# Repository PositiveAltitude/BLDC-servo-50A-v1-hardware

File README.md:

# 50A BLDC Servo Motor
This is an attempt to create a servomotor board for BLDC motors capable of providing 50A continuous current. 

Work in progress...

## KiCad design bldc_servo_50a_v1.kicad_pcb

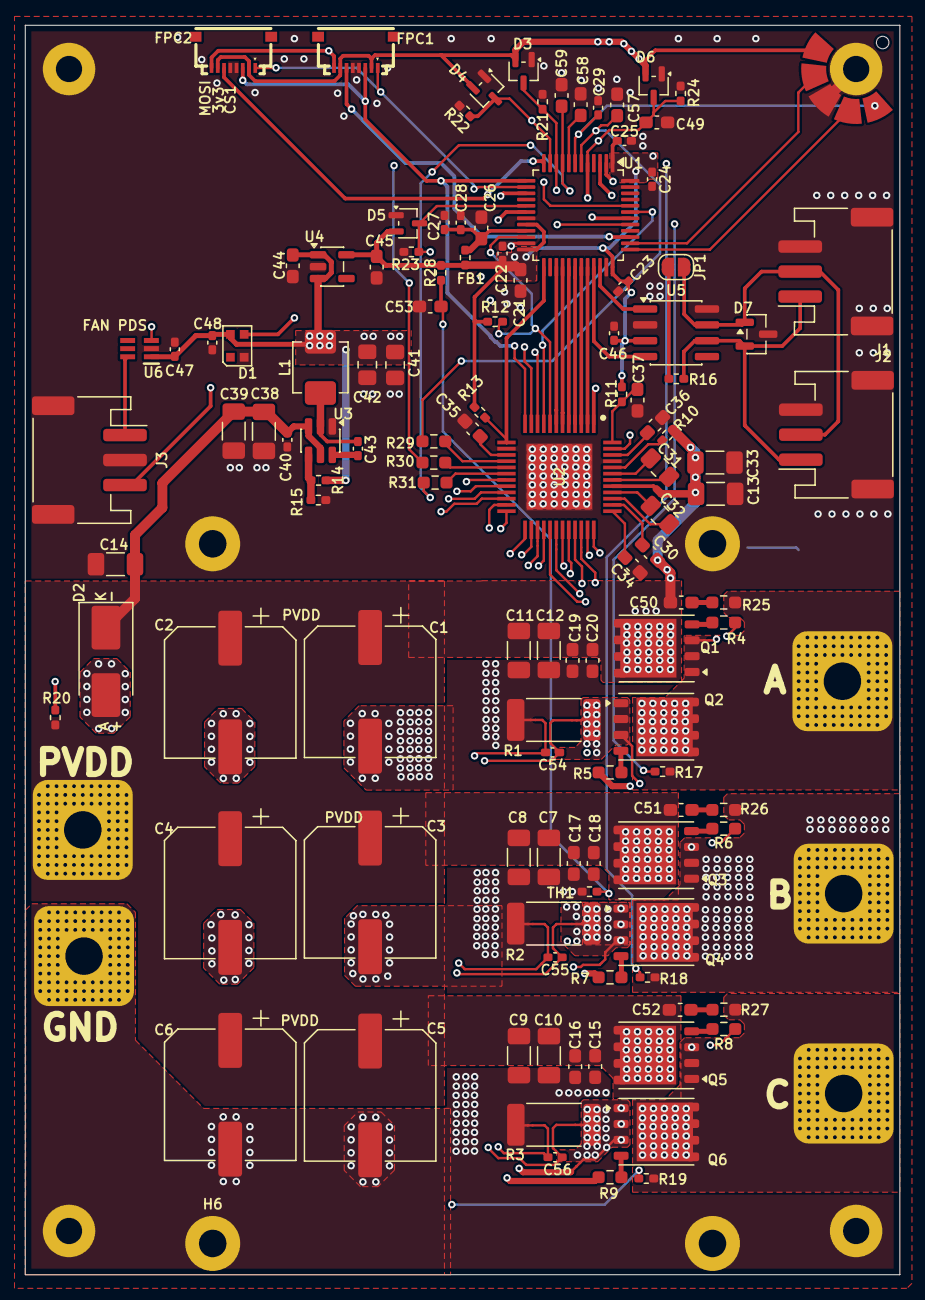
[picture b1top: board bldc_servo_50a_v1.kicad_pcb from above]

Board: 4 copper layers, 70.0 x 100.0 mm, 143 parts (0 on the bottom side), 90 nets.

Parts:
C1, C2, C3, C4, C5, C6: 100u; CP_Elec_10x7.9
C7, C8, C9, C10, C11, C12, C13, C14, C33, C38, C39: 4.7u; C_1206_3216Metric_Pad1.33x1.80mm_HandSolder
C15, C16, C17, C18, C19, C20, C26, C34, C35, C36, C37, C44, C45, C49, C53, C57, C58, C59: 1u; C_0603_1608Metric_Pad1.08x0.95mm_HandSolder
C21: 4.7u; C_0603_1608Metric_Pad1.08x0.95mm_HandSolder
C22, C23, C24, C25, C27, C29, C40, C43, C46, C47, C48: 100n; C_0402_1005Metric_Pad0.74x0.62mm_HandSolder
C28: 10n; C_0402_1005Metric_Pad0.74x0.62mm_HandSolder
C30: 2.2u; C_0603_1608Metric_Pad1.08x0.95mm_HandSolder
C31, C32: 47n; C_0805_2012Metric_Pad1.18x1.45mm_HandSolder
C41, C42: 22u; C_0805_2012Metric_Pad1.18x1.45mm_HandSolder
C50, C51, C52: 1n; C_0603_1608Metric_Pad1.08x0.95mm_HandSolder
C54, C55, C56: 1n; C_0402_1005Metric_Pad0.74x0.62mm_HandSolder
D1: WS2812B-2020; LED_WS2812B-2020_PLCC4_2.0x2.0mm
D2: SMBJ28A; D_SMB_Handsoldering
D3, D4, D5, D6: BAT54SW; SOT-323_SC-70
D7: SM712_SOT23; SOT-23
FB1: BLM15AG601SN1D; R_0402_1005Metric_Pad0.72x0.64mm_HandSolder
FPC1: Encoder1; FPC-SMD_8P-P0.50_HC-FPC-05-09-8RLTAG
FPC2: Encoder2; FPC-SMD_8P-P0.50_HC-FPC-05-09-8RLTAG
H1, H2, H3: Positive_Altitude_M2_Hole
H4, H5, H6, H7: MountingHole_2.2mm_M2_Pad
J1: CAN1; JST_PH_S3B-PH-SM4-TB_1x03-1MP_P2.00mm_Horizontal
J2: CAN2; JST_PH_S3B-PH-SM4-TB_1x03-1MP_P2.00mm_Horizontal
J3: FAN; JST_PH_S3B-PH-SM4-TB_1x03-1MP_P2.00mm_Horizontal
J5: SWD; Positive_Altitude_SWD_Connector
JP1: Enable_CAN_Termination_1; SolderJumper-2_P1.3mm_Open_RoundedPad1.0x1.5mm
L1: 3.3u; L_Changjiang_FXL0420
NT1, NT2, NT3, NT4, NT5, NT6, NT7, NT8, NT9, NT10, NT11, NT12: NetTie_2; NetTie-2_SMD_Pad0.2mm
P1: PVDD; Soldering_Pad_8mm_3mm_hole
P2: GND; Soldering_Pad_8mm_3mm_hole
P3: PHASE_A; Soldering_Pad_8mm_3mm_hole
P4: PHASE_B; Soldering_Pad_8mm_3mm_hole
P5: PHASE_C; Soldering_Pad_8mm_3mm_hole
Q1, Q2, Q3, Q4, Q5, Q6: BSC010N04LS; Infineon_PG-TDSON-8_6.15x5.15mm
R1, R2, R3: 1m; R_2512_6332Metric_Pad1.40x3.35mm_HandSolder
R4, R5, R6, R7, R8, R9: 2.2; R_0603_1608Metric_Pad0.98x0.95mm_HandSolder
R10: 100; R_0402_1005Metric_Pad0.72x0.64mm_HandSolder
R11: 220; R_0402_1005Metric_Pad0.72x0.64mm_HandSolder
R12, R13, R28: 10k; R_0402_1005Metric_Pad0.72x0.64mm_HandSolder
R14: 100k; R_0402_1005Metric_Pad0.72x0.64mm_HandSolder
R15: 13.7k; R_0402_1005Metric_Pad0.72x0.64mm_HandSolder
R16: 120; R_0402_1005Metric_Pad0.72x0.64mm_HandSolder
R17, R18, R19, R20: 39k; R_0402_1005Metric_Pad0.72x0.64mm_HandSolder
R21, R22, R23, R24: 5k; R_0402_1005Metric_Pad0.72x0.64mm_HandSolder
R25, R26, R27: 10; R_0603_1608Metric_Pad0.98x0.95mm_HandSolder
R29, R30, R31: 100; R_0603_1608Metric_Pad0.98x0.95mm_HandSolder
TH1: NCP15XH103F03RC; R_0402_1005Metric_Pad0.72x0.64mm_HandSolder
U1: STM32G431CBT6; LQFP-48_7x7mm_P0.5mm
U2: DRV8305NQPHPRQ1; QFP50P900X900X120-49N
U3: LMR51430; SOT-23-6
U4: TLV75533PDBV; SOT-23-5
U5: SN65HVD230; SOIC-8_3.9x4.9mm_P1.27mm
U6: TPS22919DCKR; SOT65P210X110-6N

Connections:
+3.3V: C21.2, C22.2, C23.2, C24.2, C25.2, C45.1, C46.1, D3.2 (K), D4.2 (K), D5.2 (K), D6.2 (K), FB1.1, FPC1.2, FPC1.7, FPC2.2, FPC2.7, J5.1 (+3.3V), R11.1, R12.1, R13.1, R28.1, U1.1 (VBAT), U1.20 (VREF+), U1.24 (VDD), U1.36 (VDD), U1.48 (VDD), U4.5 (OUT), U5.3 (VCC)
+3.3VA: C26.1, C27.1, C28.1, FB1.2, U1.21 (VDDA)
+5V: C41.1, C42.1, C44.1, C47.1, C48.2, D1.4 (VDD), L1.1, R14.1, U4.1 (IN), U4.3 (EN), U6.1 (IN)
/5V_BOOT: C43.2, U3.6 (CB)
/5V_FB: R14.2, R15.1, U3.4 (FB)
/5V_SW: C43.1, L1.2, U3.2 (SW)
/CAN_H: D7.1 (A1), J1.2, J2.2, JP1.2 (B), U5.7 (CANH)
/CAN_L: D7.2 (A2), J1.1, J2.1, R16.2, U5.6 (CANL)
/CAN_RX: U1.33 (PA11), U5.4 (R)
/CAN_TX: U1.34 (PA12), U5.1 (D)
/CS_1: FPC2.6, U1.12 (PA4)
/CS_2: FPC1.6, U1.39 (PA15)
/DRV_AVDD: C35.1, U2.15 (AVDD)
/DRV_CP1H: C31.1, U2.43 (CP1H)
/DRV_CP1L: C31.2, U2.42 (CP1L)
/DRV_CP2H: C32.1, U2.39 (CP2H)
/DRV_CP2L: C32.2, U2.40 (CP2L)
/DRV_CS: U1.43 (PB6), U2.9 (NSCS)
/DRV_DVDD: C36.1, U2.46 (DVDD)
/DRV_NFAULT: R12.2, U1.22 (PB10), U2.8 (NFAULT)
/DRV_PWRGD: R13.2, U1.25 (PB11), U2.13 (PWRGD)
/DRV_VCPH: C30.1, U2.38 (VCPH)
/DRV_VCP_LSD: C34.1, U2.37 (VCP_LSD)
/DRV_VDRAIN: R10.2, U2.44 (VDRAIN)
/DRV_VREG: C37.1, R11.2, U2.48 (VREG)
/DRV_WAKE: U1.3 (PC14), U2.47 (WAKE)
/EN_GATE: U1.2 (PC13), U2.1 (EN_GATE)
/FAN_5V: J3.1, U6.6 (OUT)
/FAN_EN: U1.44 (PB7), U6.3 (ON)
/FAN_PWM: J3.3, U1.41 (PB4)
/GH_A: R4.1, U2.36 (GHA)
/GH_B: R6.1, U2.29 (GHB)
/GH_C: R8.1, U2.28 (GHC)
/GL_A: R5.1, U2.33 (GLA)
/GL_B: R7.1, U2.32 (GLB)
/GL_C: R9.1, U2.25 (GLC)
/INHA: U1.32 (PA10), U2.2 (INHA)
/INHB: U1.30 (PA8), U2.4 (INHB)
/INHC: U1.28 (PB14), U2.6 (INHC)
/INLA: U1.31 (PA9), U2.3 (INLA)
/INLB: U1.29 (PB15), U2.5 (INLB)
/INLC: U1.27 (PB13), U2.7 (INLC)
/LED: D1.3 (DIN), U1.42 (PB5)
/MISO: FPC1.1, FPC2.1, U1.14 (PA6), U2.11 (SDO)
/MOSI: FPC1.8, FPC2.8, U1.15 (PA7), U2.10 (SDI)
/NRST: C29.1, J5.5 (RESET), U1.7 (PG10)
/PHASE_A: NT3.2, P3.1 (1_1), Q1.1 (S_1), Q1.2 (S_2), Q1.3 (S_3), Q2.5 (D_1), R17.1, R25.1
/PHASE_A_SENSE: D3.3 (COM), R17.2, R21.1, U1.10 (PA2)
/PHASE_B: NT8.2, P4.1 (1_1), Q3.1 (S_1), Q3.2 (S_2), Q3.3 (S_3), Q4.5 (D_1), R18.1, R26.1
/PHASE_B_SENSE: D4.3 (COM), R18.2, R22.1, U1.11 (PA3)
/PHASE_C: NT12.2, P5.1 (1_1), Q5.1 (S_1), Q5.2 (S_2), Q5.3 (S_3), Q6.5 (D_1), R19.1, R27.2
/PHASE_C_SENSE: D5.3 (COM), R19.2, R23.1, U1.17 (PB1)
/PVDD_SENSE: C49.1, D6.3 (COM), R20.2, R24.1, U1.5 (PF0)
/R_C_PhaseA: C50.1, R25.2
/R_C_PhaseB: C51.1, R26.2
/R_C_PhaseC: C52.1, R27.1
/SCK: FPC1.3, FPC2.3, U1.13 (PA5), U2.12 (SCLK)
/SH_A: NT3.1, U2.35 (SHA)
/SH_B: NT8.1, U2.30 (SHB)
/SH_C: NT12.1, U2.27 (SHC)
/SL_A: NT1.1, U2.34 (SLA)
/SL_B: NT5.1, U2.31 (SLB)
/SL_C: NT9.1, U2.26 (SLC)
/SN1: C54.2, NT4.1, U2.23 (SN1)
/SN2: C55.2, NT7.1, U2.21 (SN2)
/SN3: C56.2, NT11.1, U2.19 (SN3)
/SO1: R29.1, U2.16 (SO1)
/SO1_MCU: C57.1, R29.2, U1.6 (PF1)
/SO2: R30.1, U2.17 (SO2)
/SO2_MCU: C58.1, R30.2, U1.8 (PA0)
/SO3: R31.1, U2.18 (SO3)
/SO3_MCU: C59.1, R31.2, U1.9 (PA1)
/SP1: C54.1, NT2.1, U2.24 (SP1)
/SP1_TOP: NT1.2, NT2.2, Q2.1 (S_1), Q2.2 (S_2), Q2.3 (S_3), R1.1
/SP2: C55.1, NT6.1, U2.22 (SP2)
/SP2_TOP: NT5.2, NT6.2, Q4.1 (S_1), Q4.2 (S_2), Q4.3 (S_3), R2.1
/SP3: C56.1, NT10.1, U2.20 (SP3)
/SP3_TOP: NT9.2, NT10.2, Q6.1 (S_1), Q6.2 (S_2), Q6.3 (S_3), R3.1
/SWCLK: J5.2 (SWCLK), U1.38 (PA14)
/SWDIO: J5.4 (SWDIO), U1.37 (PA13)
/TEMP: C53.1, R28.2, TH1.1, U1.18 (PB2)
GND: C1.2, C2.2, C3.2, C4.2, C5.2, C6.2, C7.1, C8.1, C9.1, C10.1, C11.1, C12.1, C13.1, C14.1, C15.2, C16.2, C17.2, C18.2, C19.2, C20.2, C21.1, C22.1, C23.1, C24.1, C25.1, C26.2, C27.2, C28.2, C29.2, C33.2, C34.2, C35.2, C36.2, C37.2, C38.1, C39.2, C40.2, C41.2, C42.2, C44.2, C45.2, C46.2, C47.2, C48.1, C49.2, C53.2, C57.2, C58.2, C59.2, D1.2 (VSS), D2.2 (A), D3.1 (A), D4.1 (A), D5.1 (A), D6.1 (A), D7.3 (common), FPC1.4, FPC1.5, FPC2.4, FPC2.5, H1.1 (1_1), H2.1 (1_1), H3.1 (1_1), H4.1 (1_1), H5.1 (1_1), H6.1 (1_1), H7.1 (1_1), J1.3, J1.MP (MountPin), J2.3, J2.MP (MountPin), J3.2, J3.MP (MountPin), J5.3 (GND), NT4.2, NT7.2, NT11.2, P2.1 (1_1), R1.2, R2.2, R3.2, R15.2, R21.2, R22.2, R23.2, R24.2, TH1.2, U1.19 (VSSA), U1.23 (VSS), U1.35 (VSS), U1.47 (VSS), U2.14 (GND_1), U2.45 (GND_2), U2.49 (GND_3), U3.1 (GND), U4.2 (GND), U5.2 (GND), U5.8 (Rs), U6.2 (GND)
unnamed: JP1.1 (A), R16.1
unnamed: Q1.4 (G), R4.2
unnamed: Q2.4 (G), R5.2
unnamed: Q3.4 (G), R6.2
unnamed: Q4.4 (G), R7.2
unnamed: Q5.4 (G), R8.2
unnamed: Q6.4 (G), R9.2
PVDD: C1.1, C2.1, C3.1, C4.1, C5.1, C6.1, C7.2, C8.2, C9.2, C10.2, C11.2, C12.2, C13.2, C14.2, C15.1, C16.1, C17.1, C18.1, C19.1, C20.1, C30.2, C33.1, C38.2, C39.1, C40.1, C50.2, C51.2, C52.2, D2.1 (K), P1.1 (1_1), Q1.5 (D_1), Q3.5 (D_1), Q5.5 (D_1), R10.1, R20.1, U2.41 (PVDD), U3.3 (VIN), U3.5 (EN)

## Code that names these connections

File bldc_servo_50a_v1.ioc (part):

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Mcu.Name=STM32G431C(6-8-B)Tx
Mcu.Package=LQFP48
Mcu.UserName=STM32G431CBTx
PA0.Mode=IN1-Single-Ended
PA0.Signal=ADC2_IN1
PA1.Mode=IN2-Single-Ended
PA1.Signal=ADC2_IN2
PA10.Signal=S_TIM1_CH3
PA11.Mode=FDCAN_Activate
PA11.Signal=FDCAN1_RX
PA12.Mode=FDCAN_Activate
PA12.Signal=FDCAN1_TX
PA13.Mode=Serial_Wire
PA13.Signal=SYS_JTMS-SWDIO
PA14.Mode=Serial_Wire
PA14.Signal=SYS_JTCK-SWCLK
PA15.GPIOParameters=GPIO_Label
PA15.GPIO_Label=SPI1_NSS_ALTERNTIVE
PA15.Signal=GPIO_Input
PA2.Mode=IN3-Single-Ended
PA2.Signal=ADC1_IN3
PA3.Mode=IN4-Single-Ended
PA3.Signal=ADC1_IN4
PA4.Mode=NSS_Signal_Hard_Output
PA4.Signal=SPI1_NSS
PA5.Mode=Full_Duplex_Master
PA5.Signal=SPI1_SCK
PA6.Mode=Full_Duplex_Master
PA6.Signal=SPI1_MISO
PA7.Mode=Full_Duplex_Master
PA7.Signal=SPI1_MOSI
PA8.Signal=S_TIM1_CH1
PA9.Signal=S_TIM1_CH2
PB1.Mode=IN12-Single-Ended
PB1.Signal=ADC1_IN12
PB13.Mode=PWM Generation1 CH1 CH1N
PB13.Signal=TIM1_CH1N
PB14.Mode=PWM Generation2 CH2 CH2N
PB14.Signal=TIM1_CH2N
PB15.Mode=Output Compare3 CH3 CH3N
PB15.Signal=TIM1_CH3N
PB2.Mode=IN12-Single-Ended
PB2.Signal=ADC2_IN12
PB3.GPIOParameters=GPIO_Label
PB3.GPIO_Label=SPI3_SCK(UNUSED)
PB3.Mode=TX_Only_Simplex_Unidirect_Master
PB3.Signal=SPI3_SCK
PB4.GPIOParameters=GPIO_Label
PB4.GPIO_Label=TIM16_CH1(FAN)
PB4.Signal=S_TIM16_CH1
PB5.GPIOParameters=GPIO_Label
PB5.GPIO_Label=SPI3_MOSI(LED)
PB5.Mode=TX_Only_Simplex_Unidirect_Master
PB5.Signal=SPI3_MOSI
PB8-BOOT0.GPIOParameters=GPIO_Label
PB8-BOOT0.GPIO_Label=BOOT0
PB8-BOOT0.Signal=GPIO_Input
PF0-OSC_IN.Mode=IN10-Single-Ended
PF0-OSC_IN.Signal=ADC1_IN10
PF1-OSC_OUT.Mode=IN10-Single-Ended
PF1-OSC_OUT.Signal=ADC2_IN10
RCC.HSE_VALUE=8000000
RCC.SYSCLKFreq_VALUE=16000000
board=custom

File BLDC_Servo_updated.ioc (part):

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Mcu.Name=STM32G431C(6-8-B)Tx
Mcu.Package=LQFP48
Mcu.UserName=STM32G431CBTx
PA0.Mode=IN1-Differential
PA0.Signal=ADC1_IN1
PA1.Mode=IN1-Differential
PA1.Signal=ADC1_IN2
PA10.Signal=S_TIM1_CH3
PA11.Mode=FDCAN_Activate
PA11.Signal=FDCAN1_RX
PA12.Mode=FDCAN_Activate
PA12.Signal=FDCAN1_TX
PA2.Mode=IN3-Differential
PA2.Signal=ADC1_IN3
PA3.Mode=IN3-Differential
PA3.Signal=ADC1_IN4
PA4.Signal=SPI1_NSS
PA5.Signal=SPI1_SCK
PA6.Signal=SPI1_MISO
PA7.Signal=SPI1_MOSI
PA8.Signal=S_TIM1_CH1
PA9.Signal=S_TIM1_CH2
PB0.Signal=TIM1_CH2N
PB1.Signal=TIM1_CH3N
PB10.Signal=GPIO_Input
PB11.Signal=GPIO_Input
PB12.Signal=SPI2_NSS
PB13.Signal=TIM1_CH1N
PB2.Signal=GPIO_Output
PB3.Signal=S_TIM2_CH2
PB4.Signal=GPIO_Output
PB6.Signal=S_TIM8_CH1
PC13.Signal=GPIO_Output
PC14-OSC32_IN.Signal=GPIO_Output
RCC.HSE_VALUE=8000000
RCC.SYSCLKFreq_VALUE=16000000
board=custom

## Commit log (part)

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2025-08-10 Add LICENSE
2025-08-10 README and TODO
2025-08-11 Example commit
2025-08-12 created fresh schematic, only added MCU and Mosfets. Pushing to save progress
2025-08-12 driver and mosfets connections
2025-08-13 MCU and essentials added
2025-09-05 Added CAN, LDO, JST to Encoder. yet to add LEDs, and currenting limitng switch for Fan.
2025-09-14 Fixes after first pass
2025-09-25 Changes after fixes-1 done
2025-10-09 STM CubeIDE-necessary pin assignments in schematic included
2025-10-09 Add files via upload
    Previous .ioc file wasnt reflecting changes so added new one
2025-10-15 Added FAN JST
2025-11-07 Completed full schematic. No ERC errors. Need to be reviewed once.
2025-11-07 Some corrections with FAN Switch
2025-11-10 Added some footprints
2025-11-13 added more footprints
2025-11-13 added more footprints, 5v buck.
2025-12-02 Added some nore footprints
2026-01-04 Changed 5V buck, LDO, shunts
2026-01-11 FETs placed
2026-01-12 Basic tentative component placement for MCU and DRV
2026-01-17 Removed duplicate V_Sensing
2026-01-17 Structure for PCB, tentative
2026-02-03 Update TODO
2026-02-06 Update TODO, schematic improvements.
2026-02-08 Assign all footprints
2026-02-18 Wip: before fixing footprints
2026-02-19 Schematic done
2026-02-21 Some small changes
2026-02-21 Tentative placement of FETs in PCB
2026-02-22 Placing DRV, Bulk caps, FETs
2026-02-23 Some more component placement
2026-03-17 Some routing done
2026-03-17 Placement of caps
2026-05-21 Placement changed
2026-05-25 Changed Phases placement
2026-05-27 Added TVS for CAN
2026-05-27 Tentative Component placement
2026-05-30 Placement Iteration 2
2026-06-23 Some routing
2026-06-24 Some routing, added RC filters for SOx
2026-06-25 Routing
